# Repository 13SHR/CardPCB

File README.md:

# PCBs
This repo includes:
- PCB of an electronic visit card
- PCB of a more complex circuit board, with custom shape
  - 3D model in .wrl archive
  - PCB file
  - Schematic file
  - Gerber files
  - Render of a top view of the board

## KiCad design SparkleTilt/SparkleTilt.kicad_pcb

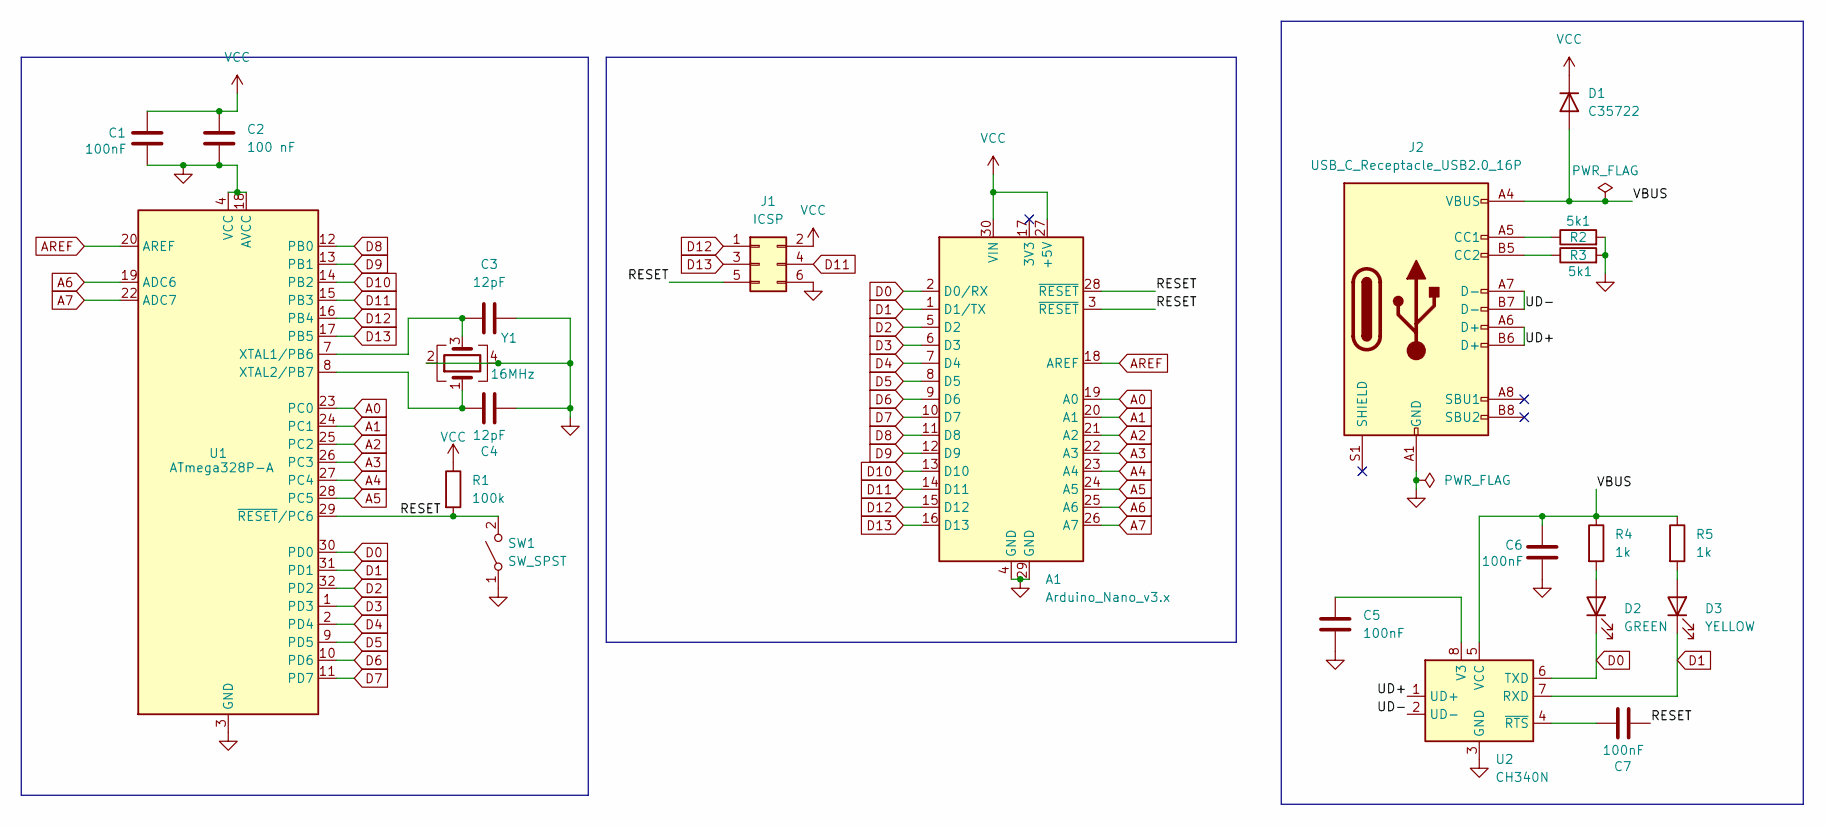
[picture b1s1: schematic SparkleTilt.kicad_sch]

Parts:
A1: Arduino_Nano_v3.x; Arduino_Nano_WithMountingHoles
C1, C5, C6, C7: 100nF; C_0805_2012Metric_Pad1.18x1.45mm_HandSolder
C2: 100 nF; C_0805_2012Metric_Pad1.18x1.45mm_HandSolder
C3, C4: 12pF; C_0805_2012Metric_Pad1.18x1.45mm_HandSolder
D1: C35722; D_SMC_Handsoldering
D2: GREEN; LED_0805_2012Metric_Pad1.15x1.40mm_HandSolder
D3: YELLOW; LED_0805_2012Metric_Pad1.15x1.40mm_HandSolder
J1: ICSP; PinHeader_2x03_P2.54mm_Vertical
J2: USB_C_Receptacle_USB2.0_16P; USB_C_Receptacle_HRO_TYPE-C-31-M-12
R1: 100k; R_0805_2012Metric_Pad1.20x1.40mm_HandSolder
R2, R3: 5k1; R_0805_2012Metric_Pad1.20x1.40mm_HandSolder
R4, R5: 1k; R_0805_2012Metric_Pad1.20x1.40mm_HandSolder
SW1: SW_SPST; SW_DIP_SPSTx04_Slide_Omron_A6H-4101_W6.15mm_P1.27mm
U1: ATmega328P-A; TQFP-32_7x7mm_P0.8mm
U2: CH340N; SOP-8_3.9x4.9mm_P1.27mm; LCSC C2977777
Y1: 16MHz; Crystal_SMD_3225-4Pin_3.2x2.5mm_HandSoldering

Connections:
/RESET: A1.3 (~RESET), A1.28 (~RESET), C7.2, J1.5, R1.2, SW1.2 (B), U1.29 (~RESET/PC6)
/UD+: J2.A6 (D+), J2.B6 (D+), U2.1 (UD+)
/UD-: J2.A7 (D-), J2.B7 (D-), U2.2 (UD-)
/VBUS: C6.1, D1.2 (A), J2.A4 (VBUS), J2.A9 (VBUS), J2.B4 (VBUS), J2.B9 (VBUS), R4.1, R5.1, U2.5 (VCC)
A0: A1.19 (A0), U1.23 (PC0)
A1: A1.20 (A1), U1.24 (PC1)
A2: A1.21 (A2), U1.25 (PC2)
A3: A1.22 (A3), U1.26 (PC3)
A4: A1.23 (A4), U1.27 (PC4)
A5: A1.24 (A5), U1.28 (PC5)
A6: A1.25 (A6), U1.19 (ADC6)
A7: A1.26 (A7), U1.22 (ADC7)
AREF: A1.18 (AREF), U1.20 (AREF)
D0: A1.2 (D0/RX), D2.1 (K), U1.30 (PD0), U2.6 (TXD)
D1: A1.1 (D1/TX), D3.1 (K), U1.31 (PD1), U2.7 (RXD)
D2: A1.5 (D2), U1.32 (PD2)
D3: A1.6 (D3), U1.1 (PD3)
D4: A1.7 (D4), U1.2 (PD4)
D5: A1.8 (D5), U1.9 (PD5)
D6: A1.9 (D6), U1.10 (PD6)
D7: A1.10 (D7), U1.11 (PD7)
D8: A1.11 (D8), U1.12 (PB0)
D9: A1.12 (D9), U1.13 (PB1)
D10: A1.13 (D10), U1.14 (PB2)
D11: A1.14 (D11), J1.4, U1.15 (PB3)
D12: A1.15 (D12), J1.1, U1.16 (PB4)
D13: A1.16 (D13), J1.3, U1.17 (PB5)
GND: A1.4 (GND), A1.29 (GND), C1.1, C2.1, C3.2, C4.2, C5.2, C6.2, J1.6, J2.A1 (GND), J2.A12 (GND), J2.B1 (GND), J2.B12 (GND), R2.2, R3.2, SW1.1 (A), U1.3 (GND), U1.4 (VCC), U1.5 (GND), U1.6 (VCC), U1.18 (AVCC), U1.21 (GND), U2.3 (GND), Y1.2, Y1.4
unnamed: D2.2 (A), R4.2
unnamed: D3.2 (A), R5.2
unnamed: J2.A5 (CC1), R2.1
unnamed: J2.B5 (CC2), R3.1
unnamed: C3.1, U1.7 (XTAL1/PB6), Y1.3
unnamed: C4.1, U1.8 (XTAL2/PB7), Y1.1
unnamed: C5.1, U2.8 (V3)
unnamed: C7.1, U2.4 (~RTS)
VCC: A1.27 (+5V), A1.30 (VIN), C1.2, C2.2, D1.1 (K), J1.2, R1.1

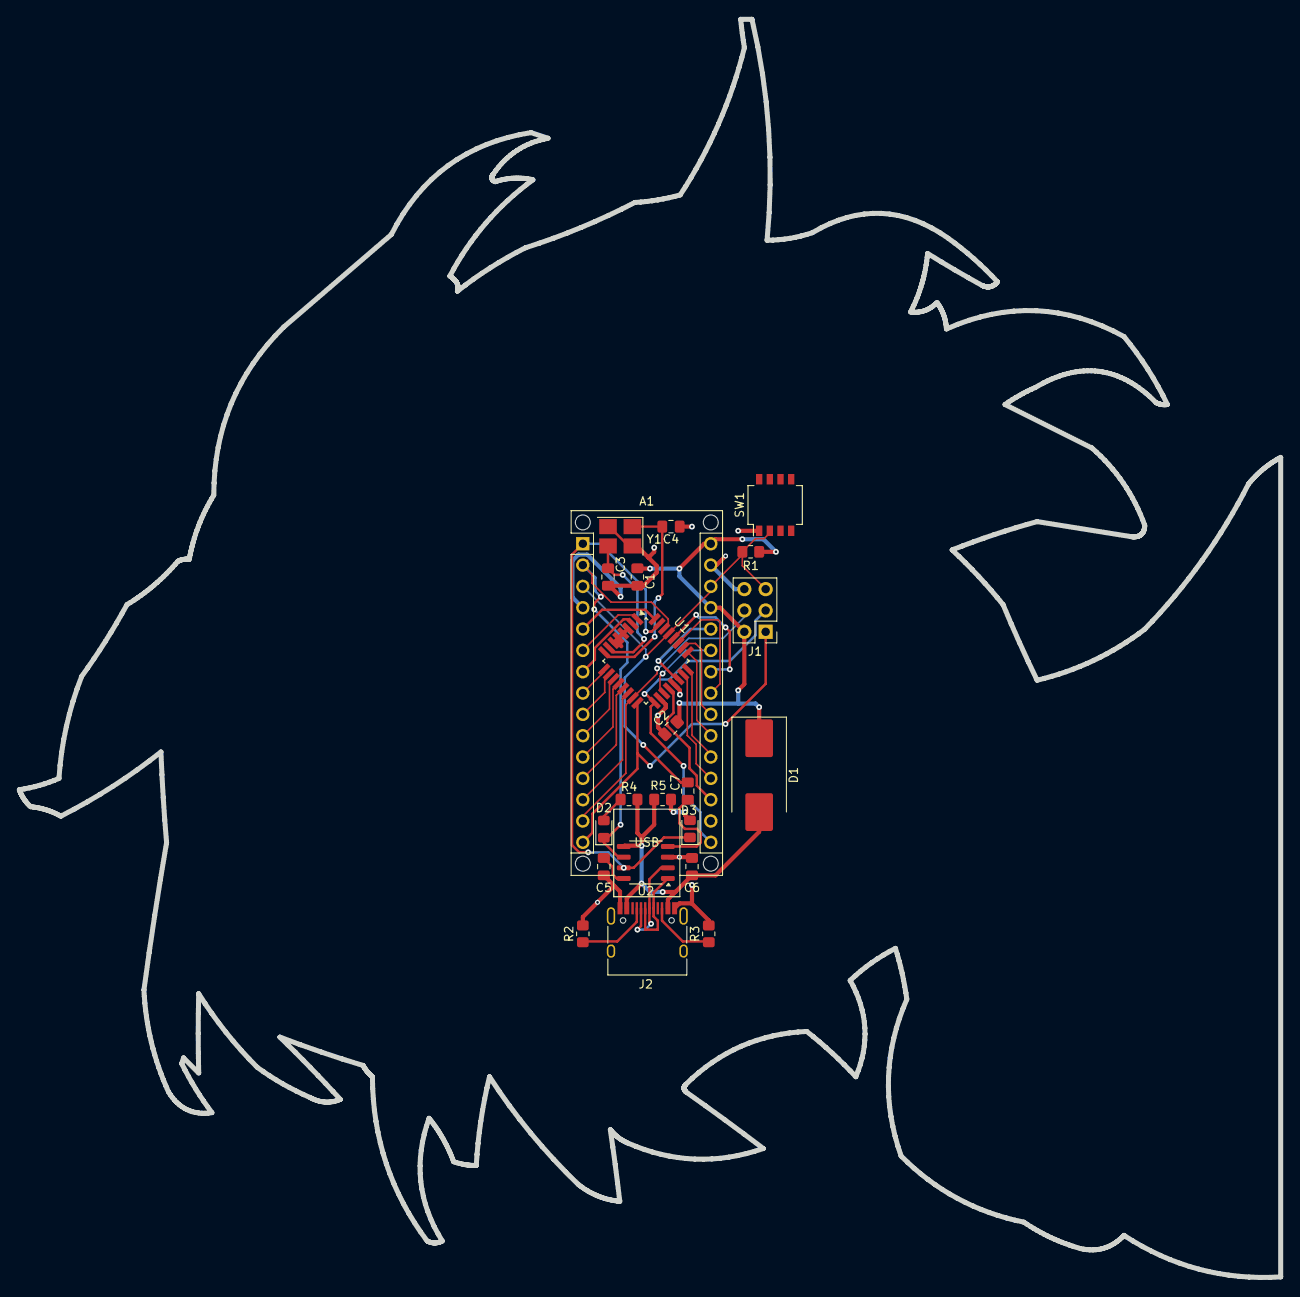
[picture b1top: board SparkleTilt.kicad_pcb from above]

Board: 2 copper layers, 150.2 x 149.8 mm, 22 parts (0 on the bottom side), 37 nets.

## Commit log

2024-08-11 Created the 3D model and the Gerber files for the PCB Card
2024-08-12 Final renders and 3D models of the PCB
2024-08-12 Added 3D Model and moved the result files to main folder
2024-08-12 GND Net Update
2024-08-15 Scrap #1
2024-08-15 Scrap #2
2024-08-15 Scrap #3
2024-08-15 Scraps #4
2024-08-15 Scraps #5
